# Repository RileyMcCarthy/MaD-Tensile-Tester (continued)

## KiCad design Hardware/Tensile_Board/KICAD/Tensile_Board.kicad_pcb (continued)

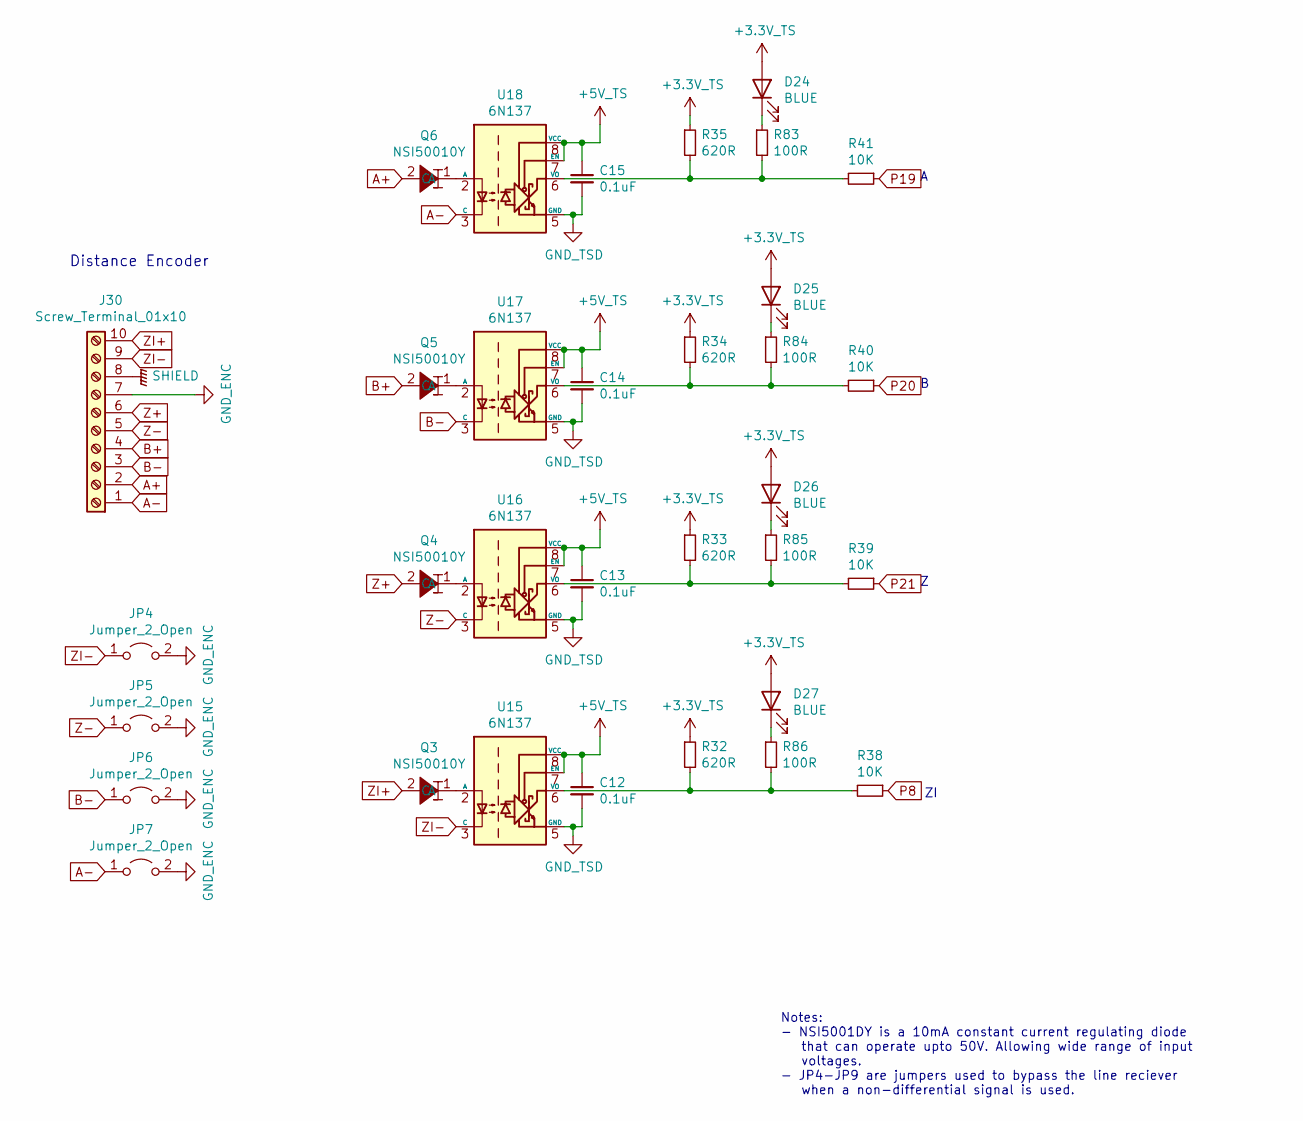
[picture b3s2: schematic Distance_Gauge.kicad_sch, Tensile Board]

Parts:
C12, C13, C14, C15: 0.1uF; C_0603_1608Metric; LCSC C14663
D24, D25, D26, D27: BLUE; LED_0603_1608Metric; LCSC C72041
J30: Screw_Terminal_01x10; TerminalBlock_4Ucon_1x10_P3.50mm_Vertical
JP4, JP5, JP6, JP7: Jumper_2_Open; PinHeader_1x02_P2.54mm_Vertical
Q3, Q4, Q5, Q6: NSI50010Y; D_SOD-123; LCSC C150049
R32, R33, R34, R35: 620R; R_0603_1608Metric; LCSC C23138
R38, R39, R40, R41: 10K; R_0603_1608Metric; LCSC C25804
R83, R84, R85, R86: 100R; R_0603_1608Metric; LCSC C22775
U15, U16, U17, U18: 6N137; SOP-8_6.62x9.15mm_P2.54mm; LCSC C110020

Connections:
GND_ENC: J30.7, JP4.2 (B), JP5.2 (B), JP6.2 (B), JP7.2 (B)
GND_TSD: C12.2, C13.2, C14.2, C15.2, U15.5 (GND), U16.5 (GND), U17.5 (GND), U18.5 (GND); also elsewhere on the board
unnamed: D24.1 (K), R83.1
unnamed: D25.1 (K), R84.1
unnamed: D26.1 (K), R85.1
unnamed: D27.1 (K), R86.1
unnamed: Q3.1 (C), U15.2 (A)
unnamed: Q4.1 (C), U16.2 (A)
unnamed: Q5.1 (C), U17.2 (A)
unnamed: Q6.1 (C), U18.2 (A)
unnamed: R32.2, R38.2, R86.2, U15.6 (VO)
unnamed: R33.2, R39.2, R85.2, U16.6 (VO)
unnamed: R34.2, R40.2, R84.2, U17.6 (VO)
unnamed: R35.2, R41.2, R83.2, U18.6 (VO)
OUTA+: J30.2, Q6.2 (A)
OUTA-: J30.1, JP7.1 (A), U18.3 (C)
OUTB+: J30.4, Q5.2 (A)
OUTB-: J30.3, JP6.1 (A), U17.3 (C)
OUTZ+: J30.6, Q4.2 (A)
OUTZ-: J30.5, JP5.1 (A), U16.3 (C)
OUTZI+: J30.10, Q3.2 (A)
OUTZI-: J30.9, JP4.1 (A), U15.3 (C)
P8: R38.1; also elsewhere on the board
P19: R41.1; also elsewhere on the board
P20: R40.1; also elsewhere on the board
P21: R39.1; also elsewhere on the board
SHIELD: J30.8; also elsewhere on the board

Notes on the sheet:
Notes: - NSI5001DY is a 10mA constant current regulating diode that can operate upto 50V. Allowing wide range of input voltages. - JP4-JP9 are jumpers used to bypass the line reciever when a non-differential signal is used.
Distance Encoder

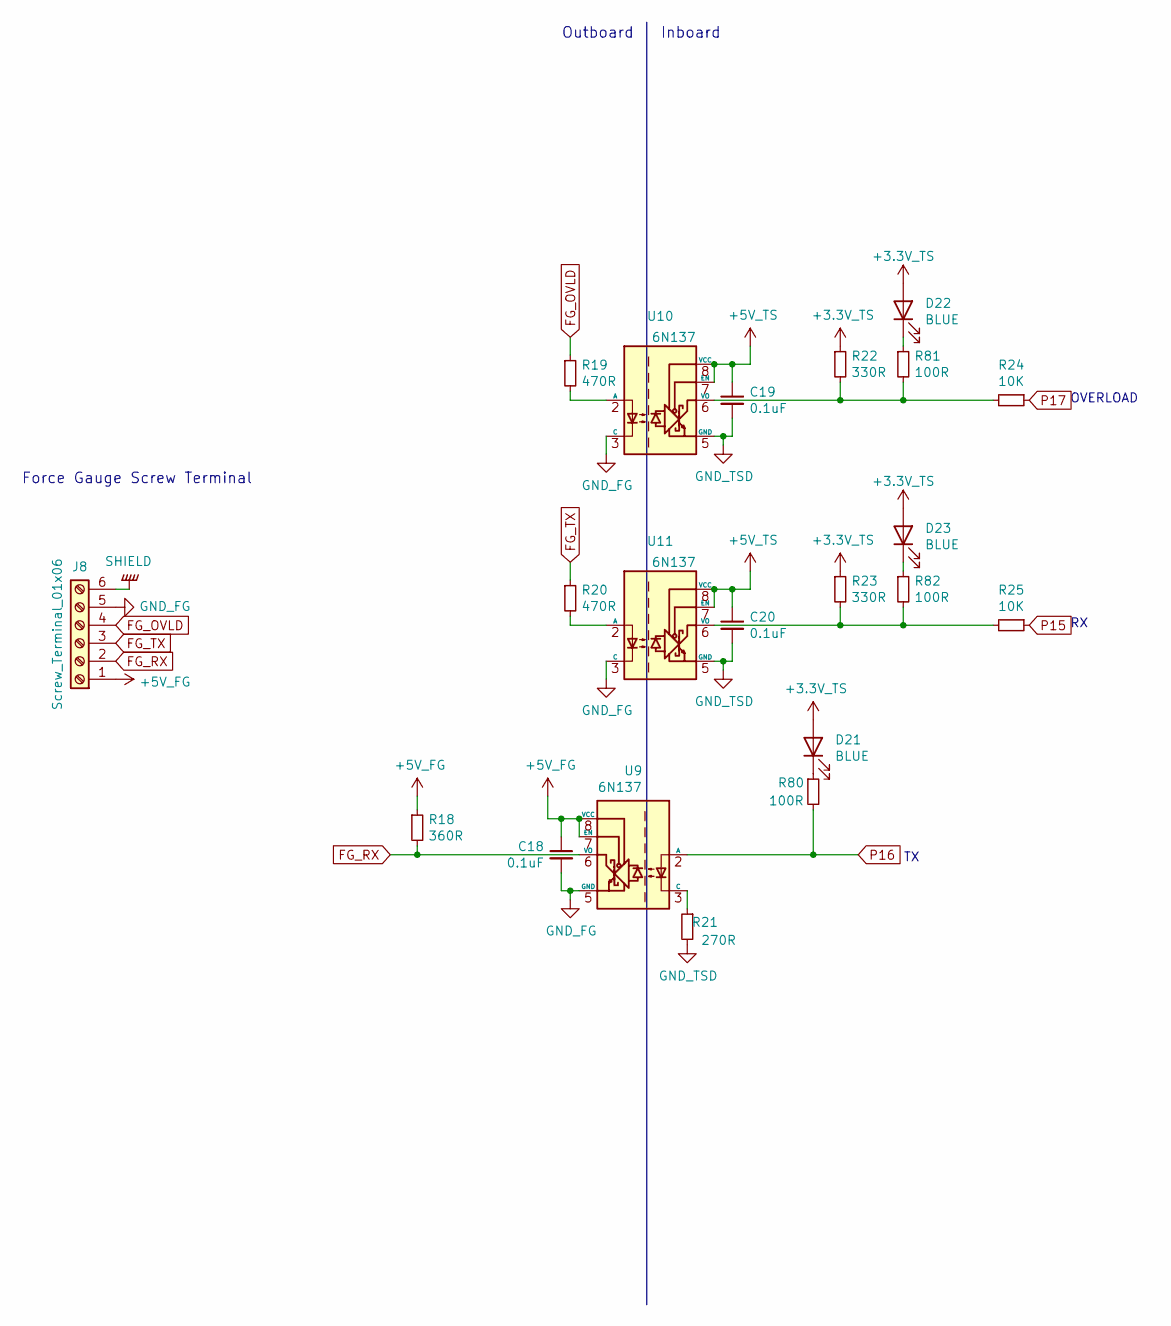
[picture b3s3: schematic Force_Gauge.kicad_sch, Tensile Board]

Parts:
C18, C19, C20: 0.1uF; C_0603_1608Metric; LCSC C14663
D21, D22, D23: BLUE; LED_0603_1608Metric; LCSC C72041
J8: Screw_Terminal_01x06; TerminalBlock_4Ucon_1x06_P3.50mm_Vertical
R18: 360R; R_0603_1608Metric; LCSC C25194
R19, R20: 470R; R_0603_1608Metric; LCSC C23179
R21: 270R; R_0603_1608Metric; LCSC C22966
R22, R23: 330R; R_0603_1608Metric; LCSC C23138
R24, R25: 10K; R_0603_1608Metric; LCSC C25804
R80, R81, R82: 100R; R_0603_1608Metric; LCSC C22775
U9, U10, U11: 6N137; SOP-8_6.62x9.15mm_P2.54mm; LCSC C110020

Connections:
+5V_FG: C18.1, J8.1, R18.1, U9.7 (EN), U9.8 (VCC)
FG_OVLD: J8.4, R19.1
FG_RX: J8.2, R18.2, U9.6 (VO)
FG_TX: J8.3, R20.1
GND_FG: C18.2, J8.5, U9.5 (GND), U10.3 (C), U11.3 (C)
GND_TSD: C19.2, C20.2, R21.2, U10.5 (GND), U11.5 (GND); also elsewhere on the board
unnamed: D21.1 (K), R80.1
unnamed: D22.1 (K), R81.1
unnamed: D23.1 (K), R82.1
unnamed: R19.2, U10.2 (A)
unnamed: R20.2, U11.2 (A)
unnamed: R21.1, U9.3 (C)
unnamed: R22.2, R24.2, R81.2, U10.6 (VO)
unnamed: R23.2, R25.2, R82.2, U11.6 (VO)
P15: R25.1; also elsewhere on the board
P16: R80.2, U9.2 (A); also elsewhere on the board
P17: R24.1; also elsewhere on the board
SHIELD: J8.6; also elsewhere on the board

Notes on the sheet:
OVERLOAD
Outboard
Inboard
Force Gauge Screw Terminal

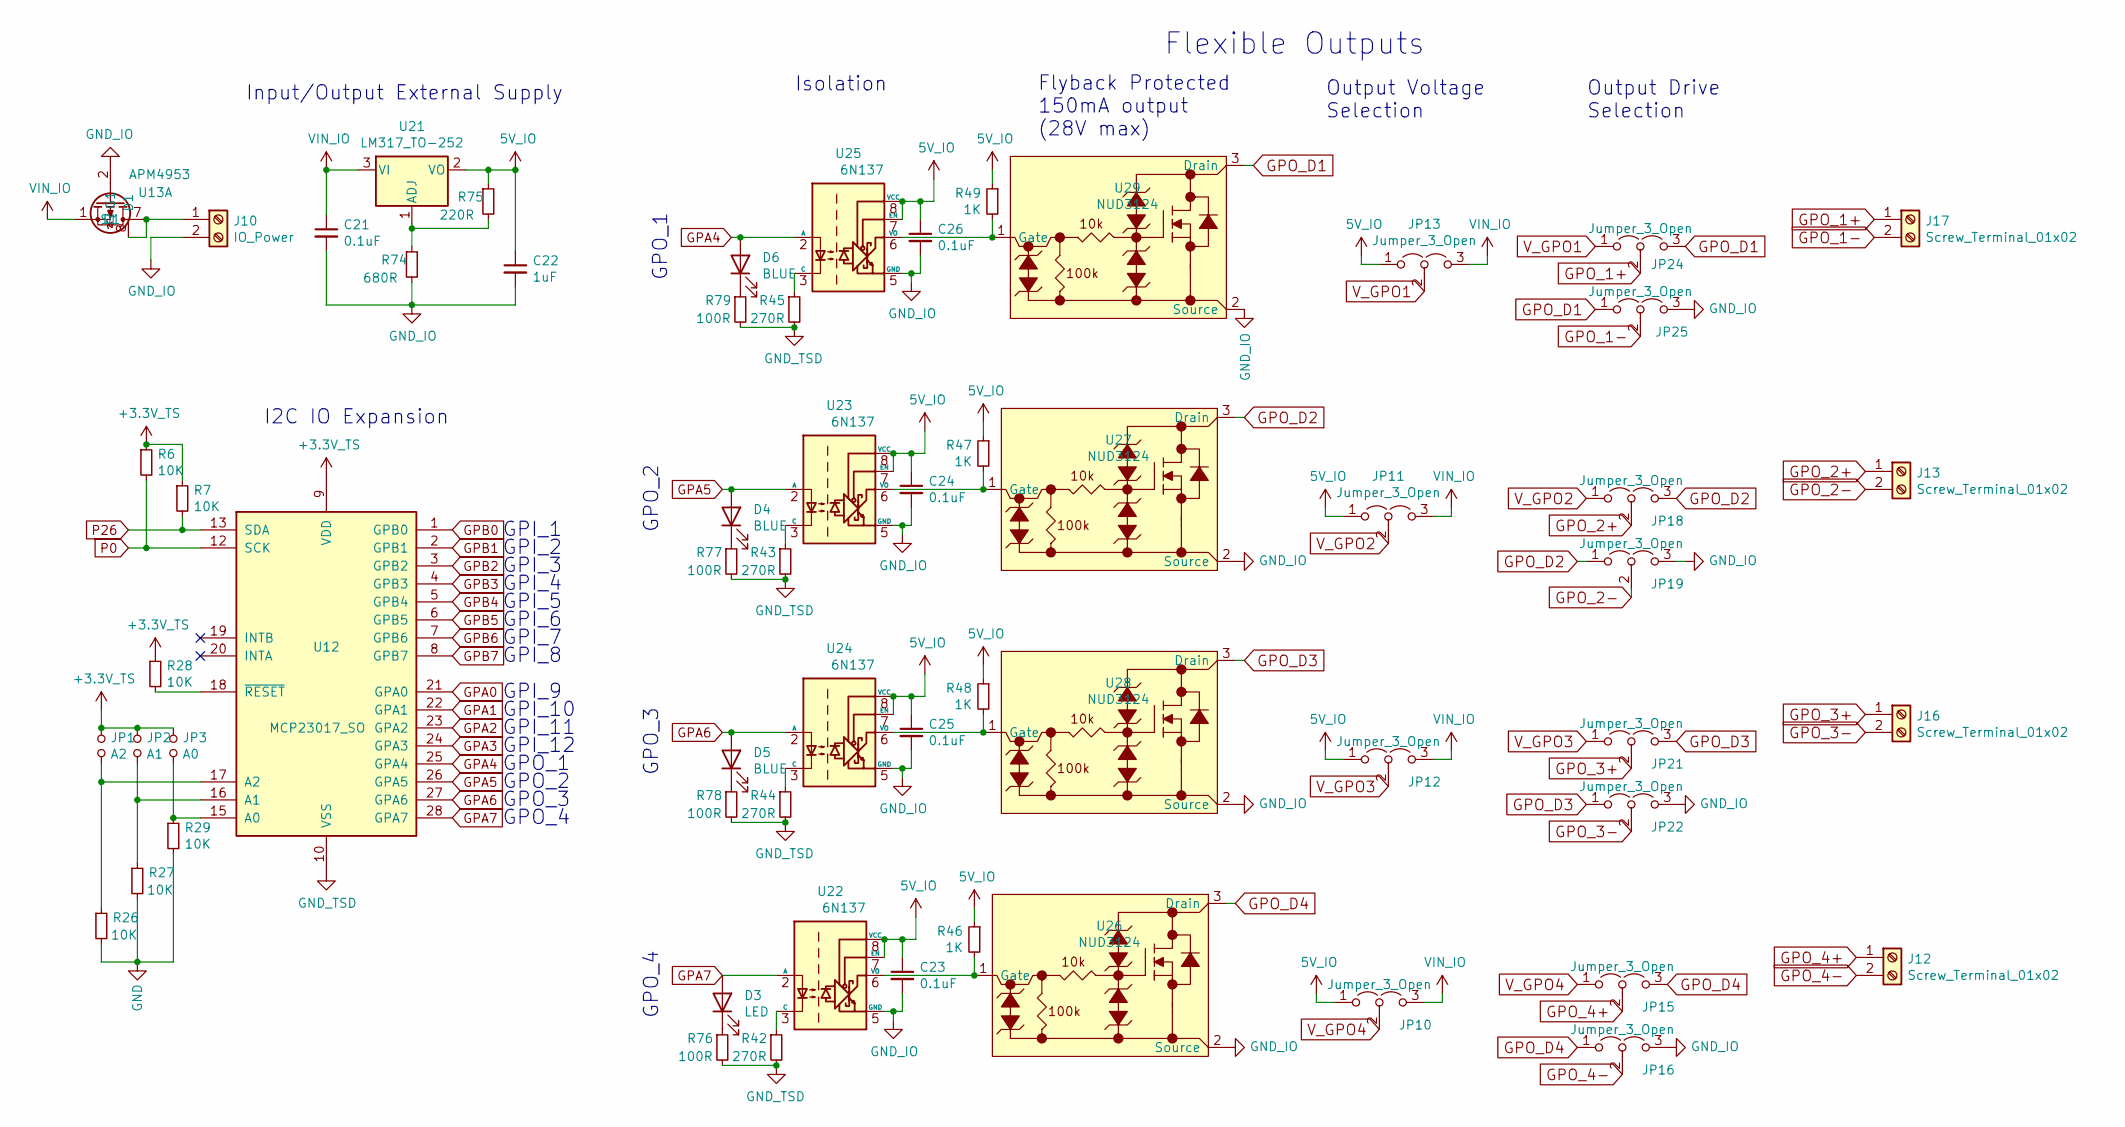
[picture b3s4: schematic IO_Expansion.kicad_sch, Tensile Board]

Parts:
C21: 0.1uF; C_0805_2012Metric; LCSC C49678
C22: 1uF; C_0805_2012Metric; LCSC C28323
C23, C24, C25, C26: 0.1uF; C_0603_1608Metric; LCSC C14663
D3: LED; LED_0603_1608Metric; LCSC C72041
D4, D5, D6: BLUE; LED_0603_1608Metric; LCSC C72041
J10: IO_Power; TerminalBlock_bornier-2_P5.08mm
J12, J13, J16, J17: Screw_Terminal_01x02; TerminalBlock_4Ucon_1x02_P3.50mm_Vertical
JP1: A2; SolderJumper-2_P1.3mm_Open_Pad1.0x1.5mm
JP2: A1; SolderJumper-2_P1.3mm_Open_Pad1.0x1.5mm
JP3: A0; SolderJumper-2_P1.3mm_Open_Pad1.0x1.5mm
JP10, JP11, JP12, JP13, JP15, JP16, JP18, JP19, JP21, JP22, JP24, JP25: Jumper_3_Open; PinHeader_1x03_P2.54mm_Vertical
R6, R7, R26, R27, R28, R29: 10K; R_0603_1608Metric; LCSC C25804
R42, R43, R44, R45: 270R; R_0603_1608Metric; LCSC C22966
R46, R47, R48, R49: 1K; R_0603_1608Metric; LCSC C21190
R74: 680R; R_0603_1608Metric; LCSC C23228
R75: 220R; R_0603_1608Metric; LCSC C22962
R76, R77, R78, R79: 100R; R_0603_1608Metric; LCSC C22775
U12: MCP23017_SO; SOIC-28W_7.5x17.9mm_P1.27mm; LCSC C47023
U13: APM4953; SOP-8_3.9x4.9mm_P1.27mm; LCSC C20897
U21: LM317_TO-252; TO-252-2; LCSC C75510
U22, U23, U24, U25: 6N137; SOP-8_6.62x9.15mm_P2.54mm; LCSC C110020
U26, U27, U28, U29: NUD3124; SOT-23; LCSC C85758

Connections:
5V_IO: C22.1, C23.1, C24.1, C25.1, C26.1, JP10.1 (A), JP11.1 (A), JP12.1 (A), JP13.1 (A), R46.1, R47.1, R48.1, R49.1, R75.1, U21.2 (VO), U22.7 (EN), U22.8 (VCC), U23.7 (EN), U23.8 (VCC), U24.7 (EN), U24.8 (VCC), U25.7 (EN), U25.8 (VCC); also elsewhere on the board
GND: R26.2, R27.2, R29.2
GND_IO: C21.2, C22.2, C23.2, C24.2, C25.2, C26.2, J10.2, JP16.3 (B), JP19.3 (B), JP22.3 (B), JP25.3 (B), R74.2, U13.2 (G1), U22.5 (GND), U23.5 (GND), U24.5 (GND), U25.5 (GND), U26.2 (Source), U27.2 (Source), U28.2 (Source), U29.2 (Source); also elsewhere on the board
GND_TSD: R42.2, R43.2, R44.2, R45.2, R76.2, R77.2, R78.2, R79.2, U12.10 (VSS); also elsewhere on the board
GPA0: U12.21 (GPA0); also elsewhere on the board
GPA1: U12.22 (GPA1); also elsewhere on the board
GPA2: U12.23 (GPA2); also elsewhere on the board
GPA3: U12.24 (GPA3); also elsewhere on the board
GPA4: D6.2 (A), U12.25 (GPA4), U25.2 (A)
GPA5: D4.2 (A), U12.26 (GPA5), U23.2 (A)
GPA6: D5.2 (A), U12.27 (GPA6), U24.2 (A)
GPA7: D3.2 (A), U12.28 (GPA7), U22.2 (A)
GPB0: U12.1 (GPB0); also elsewhere on the board
GPB1: U12.2 (GPB1); also elsewhere on the board
GPB2: U12.3 (GPB2); also elsewhere on the board
GPB3: U12.4 (GPB3); also elsewhere on the board
GPB4: U12.5 (GPB4); also elsewhere on the board
GPB5: U12.6 (GPB5); also elsewhere on the board
GPB6: U12.7 (GPB6); also elsewhere on the board
GPB7: U12.8 (GPB7); also elsewhere on the board
GPO_1+: J17.1, JP24.2 (C)
GPO_1-: J17.2, JP25.2 (C)
GPO_2+: J13.1, JP18.2 (C)
GPO_2-: J13.2, JP19.2 (C)
GPO_3+: J16.1, JP21.2 (C)
GPO_3-: J16.2, JP22.2 (C)
GPO_4+: J12.1, JP15.2 (C)
GPO_4-: J12.2, JP16.2 (C)
GPO_D1: JP24.3 (B), JP25.1 (A), U29.3 (Drain)
GPO_D2: JP18.3 (B), JP19.1 (A), U27.3 (Drain)
GPO_D3: JP21.3 (B), JP22.1 (A), U28.3 (Drain)
GPO_D4: JP15.3 (B), JP16.1 (A), U26.3 (Drain)
unnamed: D3.1 (K), R76.1
unnamed: D4.1 (K), R77.1
unnamed: D5.1 (K), R78.1
unnamed: D6.1 (K), R79.1
unnamed: J10.1, U13.7 (D1), U13.8 (D1)
unnamed: JP1.2, R26.1, U12.17 (A2)
unnamed: JP2.2, R27.1, U12.16 (A1)
unnamed: JP3.2, R29.1, U12.15 (A0)
unnamed: R28.2, U12.18 (~RESET)
unnamed: R42.1, U22.3 (C)
unnamed: R43.1, U23.3 (C)
unnamed: R44.1, U24.3 (C)
unnamed: R45.1, U25.3 (C)
unnamed: R46.2, U22.6 (VO), U26.1 (Gate)
unnamed: R47.2, U23.6 (VO), U27.1 (Gate)
unnamed: R48.2, U24.6 (VO), U28.1 (Gate)
unnamed: R49.2, U25.6 (VO), U29.1 (Gate)
unnamed: R74.1, R75.2, U21.1 (ADJ)
VIN_IO: C21.1, JP10.3 (B), JP11.3 (B), JP12.3 (B), JP13.3 (B), U13.1 (S1), U21.3 (VI)
V_GPO1: JP13.2 (C), JP24.1 (A)
V_GPO2: JP11.2 (C), JP18.1 (A)
V_GPO3: JP12.2 (C), JP21.1 (A)
V_GPO4: JP10.2 (C), JP15.1 (A)

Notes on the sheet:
GPI_6
GPO_3
GPI_4
Output Voltage Selection
GPI_11
Flexible Outputs
GPI_7
GPI_10
Input/Output External Supply
GPI_3
GPI_9
GPO_2
GPO_1
I2C IO Expansion
GPI_1
GPO_4
GPI_12
GPI_8
GPI_5
GPI_2
Isolation
Output Drive Selection
Flyback Protected 150mA output (28V max)

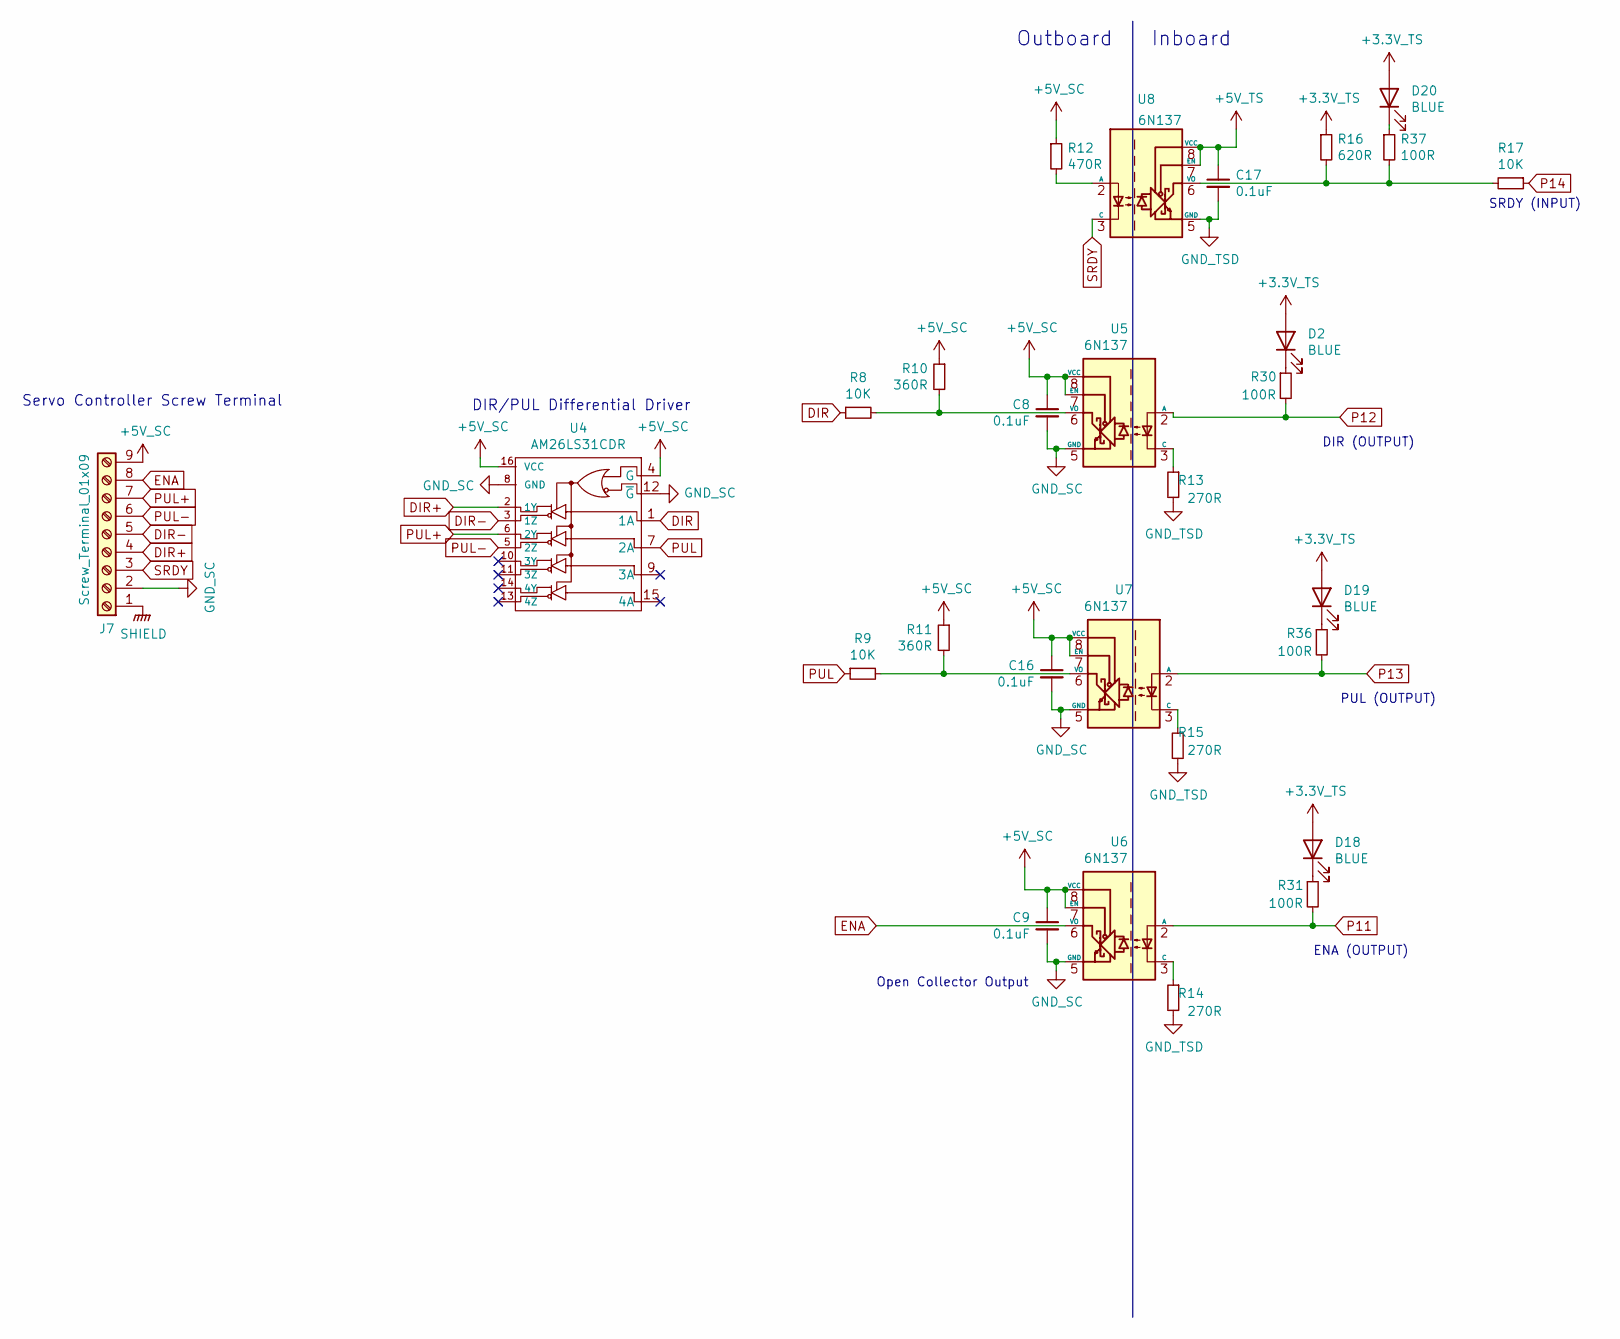
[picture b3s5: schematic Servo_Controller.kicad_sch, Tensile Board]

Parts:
C8, C9, C16, C17: 0.1uF; C_0603_1608Metric; LCSC C14663
D2, D18, D19, D20: BLUE; LED_0603_1608Metric; LCSC C72041
J7: Screw_Terminal_01x09; TerminalBlock_4Ucon_1x09_P3.50mm_Vertical
R8, R9, R17: 10K; R_0603_1608Metric; LCSC C25804
R10, R11: 360R; R_0603_1608Metric; LCSC C25194
R12: 470R; R_0603_1608Metric; LCSC C23179
R13, R14, R15: 270R; R_0603_1608Metric; LCSC C22966
R16: 620R; R_0603_1608Metric; LCSC C23138
R30, R31, R36, R37: 100R; R_0603_1608Metric; LCSC C22775
U4: AM26LS31CDR; SOIC-16_3.9x9.9mm_P1.27mm; LCSC C6179
U5, U6, U7, U8: 6N137; SOP-8_6.62x9.15mm_P2.54mm; LCSC C110020

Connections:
+5V_SC: C8.1, C9.1, C16.1, J7.9, R10.1, R11.1, R12.1, U4.4 (G), U4.16 (VCC), U5.7 (EN), U5.8 (VCC), U6.7 (EN), U6.8 (VCC), U7.7 (EN), U7.8 (VCC)
DIR: R8.1, U4.1 (1A)
DIR+: J7.4, U4.2 (1Y)
DIR-: J7.5, U4.3 (1Z)
ENA: J7.8, U6.6 (VO)
GND_SC: C8.2, C9.2, C16.2, J7.2, U4.8 (GND), U4.12 (~G), U5.5 (GND), U6.5 (GND), U7.5 (GND)
GND_TSD: C17.2, R13.2, R14.2, R15.2, U8.5 (GND); also elsewhere on the board
unnamed: D2.1 (K), R30.1
unnamed: D18.1 (K), R31.1
unnamed: D19.1 (K), R36.1
unnamed: D20.1 (K), R37.1
unnamed: R8.2, R10.2, U5.6 (VO)
unnamed: R9.2, R11.2, U7.6 (VO)
unnamed: R12.2, U8.2 (A)
unnamed: R13.1, U5.3 (C)
unnamed: R14.1, U6.3 (C)
unnamed: R15.1, U7.3 (C)
unnamed: R16.2, R17.2, R37.2, U8.6 (VO)
P11: R31.2, U6.2 (A); also elsewhere on the board
P12: R30.2, U5.2 (A); also elsewhere on the board
P13: R36.2, U7.2 (A); also elsewhere on the board
P14: R17.1; also elsewhere on the board
PUL: R9.1, U4.7 (2A)
PUL+: J7.7, U4.6 (2Y)
PUL-: J7.6, U4.5 (2Z)
SHIELD: J7.1; also elsewhere on the board
SRDY: J7.3, U8.3 (C)

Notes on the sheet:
Inboard
Servo Controller Screw Terminal
PUL (OUTPUT)
DIR (OUTPUT)
SRDY (INPUT)
DIR/PUL Differential Driver
Open Collector Output
ENA (OUTPUT)
Outboard

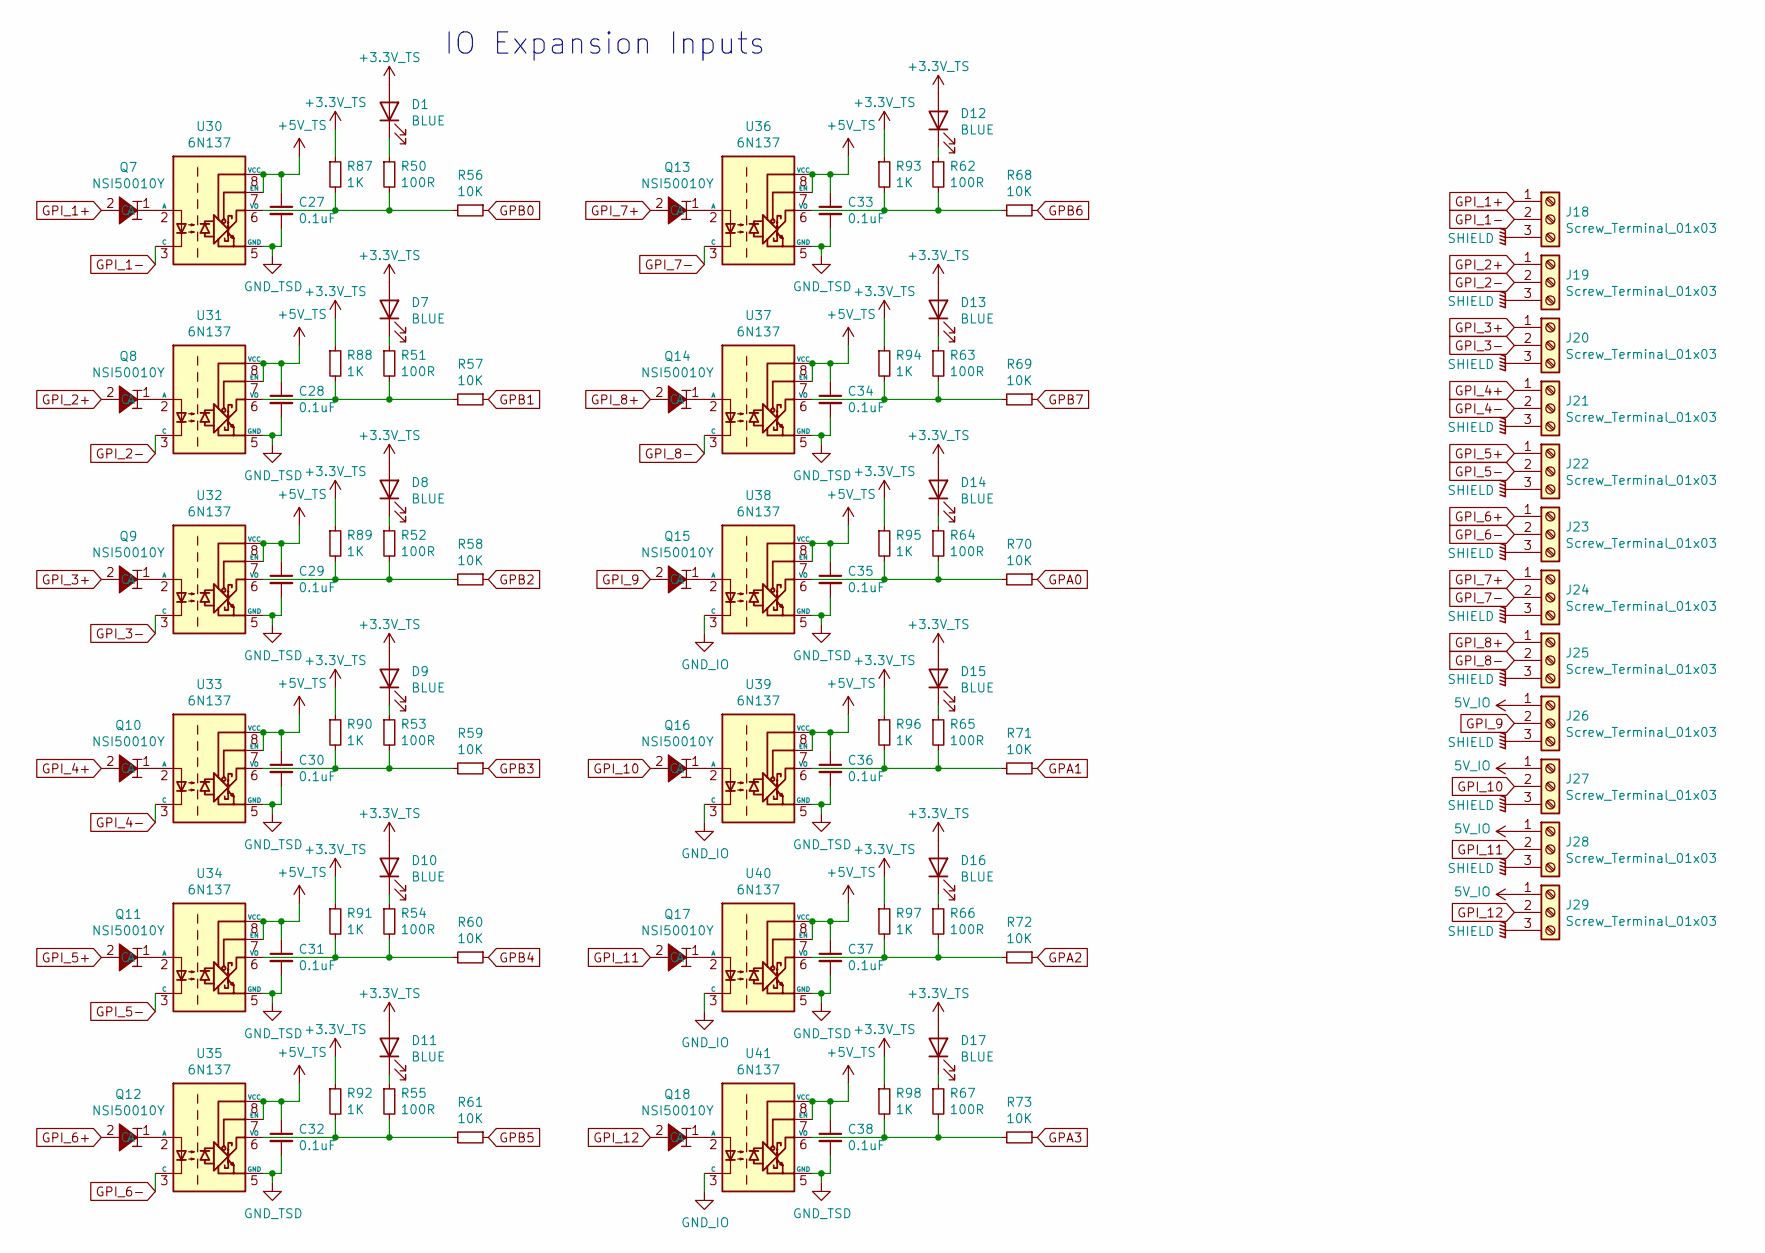
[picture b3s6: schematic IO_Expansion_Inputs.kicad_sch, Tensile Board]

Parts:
C27, C28, C29, C30, C31, C32, C33, C34, C35, C36, C37, C38: 0.1uF; C_0603_1608Metric; LCSC C14663
D1, D7, D8, D9, D10, D11, D12, D13, D14, D15, D16, D17: BLUE; LED_0603_1608Metric; LCSC C72041
J18, J19, J20, J21, J22, J23, J24, J25, J26, J27, J28, J29: Screw_Terminal_01x03; TerminalBlock_4Ucon_1x03_P3.50mm_Vertical
Q7, Q8, Q9, Q10, Q11, Q12, Q13, Q14, Q15, Q16, Q17, Q18: NSI50010Y; D_SOD-123; LCSC C150049
R50, R51, R52, R53, R54, R55, R62, R63, R64, R65, R66, R67: 100R; R_0603_1608Metric; LCSC C22775
R56, R57, R58, R59, R60, R61, R68, R69, R70, R71, R72, R73: 10K; R_0603_1608Metric; LCSC C25804
R87, R88, R89, R90, R91, R92, R93, R94, R95, R96, R97, R98: 1K; R_0603_1608Metric; LCSC C21190
U30, U31, U32, U33, U34, U35, U36, U37, U38, U39, U40, U41: 6N137; SOP-8_6.62x9.15mm_P2.54mm; LCSC C110020

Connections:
5V_IO: J26.1, J27.1, J28.1, J29.1; also elsewhere on the board
GND_IO: U38.3 (C), U39.3 (C), U40.3 (C), U41.3 (C); also elsewhere on the board
GND_TSD: C27.2, C28.2, C29.2, C30.2, C31.2, C32.2, C33.2, C34.2, C35.2, C36.2, C37.2, C38.2, U30.5 (GND), U31.5 (GND), U32.5 (GND), U33.5 (GND), U34.5 (GND), U35.5 (GND), U36.5 (GND), U37.5 (GND), U38.5 (GND), U39.5 (GND), U40.5 (GND), U41.5 (GND); also elsewhere on the board
GPA0: R70.1; also elsewhere on the board
GPA1: R71.1; also elsewhere on the board
GPA2: R72.1; also elsewhere on the board
GPA3: R73.1; also elsewhere on the board
GPB0: R56.1; also elsewhere on the board
GPB1: R57.1; also elsewhere on the board
GPB2: R58.1; also elsewhere on the board
GPB3: R59.1; also elsewhere on the board
GPB4: R60.1; also elsewhere on the board
GPB5: R61.1; also elsewhere on the board
GPB6: R68.1; also elsewhere on the board
GPB7: R69.1; also elsewhere on the board
GPI_1+: J18.1, Q7.2 (A)
GPI_1-: J18.2, U30.3 (C)
GPI_2+: J19.1, Q8.2 (A)
GPI_2-: J19.2, U31.3 (C)
GPI_3+: J20.1, Q9.2 (A)
GPI_3-: J20.2, U32.3 (C)
GPI_4+: J21.1, Q10.2 (A)
GPI_4-: J21.2, U33.3 (C)
GPI_5+: J22.1, Q11.2 (A)
GPI_5-: J22.2, U34.3 (C)
GPI_6+: J23.1, Q12.2 (A)
GPI_6-: J23.2, U35.3 (C)
GPI_7+: J24.1, Q13.2 (A)
GPI_7-: J24.2, U36.3 (C)
GPI_8+: J25.1, Q14.2 (A)
GPI_8-: J25.2, U37.3 (C)
GPI_9: J26.2, Q15.2 (A)
GPI_10: J27.2, Q16.2 (A)
GPI_11: J28.2, Q17.2 (A)
GPI_12: J29.2, Q18.2 (A)
unnamed: D1.1 (K), R50.1
unnamed: D7.1 (K), R51.1
unnamed: D8.1 (K), R52.1
unnamed: D9.1 (K), R53.1
unnamed: D10.1 (K), R54.1
unnamed: D11.1 (K), R55.1
unnamed: D12.1 (K), R62.1
unnamed: D13.1 (K), R63.1
unnamed: D14.1 (K), R64.1
unnamed: D15.1 (K), R65.1
unnamed: D16.1 (K), R66.1
unnamed: D17.1 (K), R67.1
unnamed: Q7.1 (C), U30.2 (A)
unnamed: Q8.1 (C), U31.2 (A)
unnamed: Q9.1 (C), U32.2 (A)
unnamed: Q10.1 (C), U33.2 (A)
unnamed: Q11.1 (C), U34.2 (A)
unnamed: Q12.1 (C), U35.2 (A)
unnamed: Q13.1 (C), U36.2 (A)
unnamed: Q14.1 (C), U37.2 (A)
unnamed: Q15.1 (C), U38.2 (A)
unnamed: Q16.1 (C), U39.2 (A)
unnamed: Q17.1 (C), U40.2 (A)
unnamed: Q18.1 (C), U41.2 (A)
unnamed: R50.2, R56.2, R87.2, U30.6 (VO)
unnamed: R51.2, R57.2, R88.2, U31.6 (VO)
unnamed: R52.2, R58.2, R89.2, U32.6 (VO)
unnamed: R53.2, R59.2, R90.2, U33.6 (VO)
unnamed: R54.2, R60.2, R91.2, U34.6 (VO)
unnamed: R55.2, R61.2, R92.2, U35.6 (VO)
unnamed: R62.2, R68.2, R93.2, U36.6 (VO)
unnamed: R63.2, R69.2, R94.2, U37.6 (VO)
unnamed: R64.2, R70.2, R95.2, U38.6 (VO)
unnamed: R65.2, R71.2, R96.2, U39.6 (VO)
unnamed: R66.2, R72.2, R97.2, U40.6 (VO)
unnamed: R67.2, R73.2, R98.2, U41.6 (VO)
SHIELD: J18.3, J19.3, J20.3, J21.3, J22.3, J23.3, J24.3, J25.3, J26.3, J27.3, J28.3, J29.3; also elsewhere on the board

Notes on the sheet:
IO Expansion Inputs

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
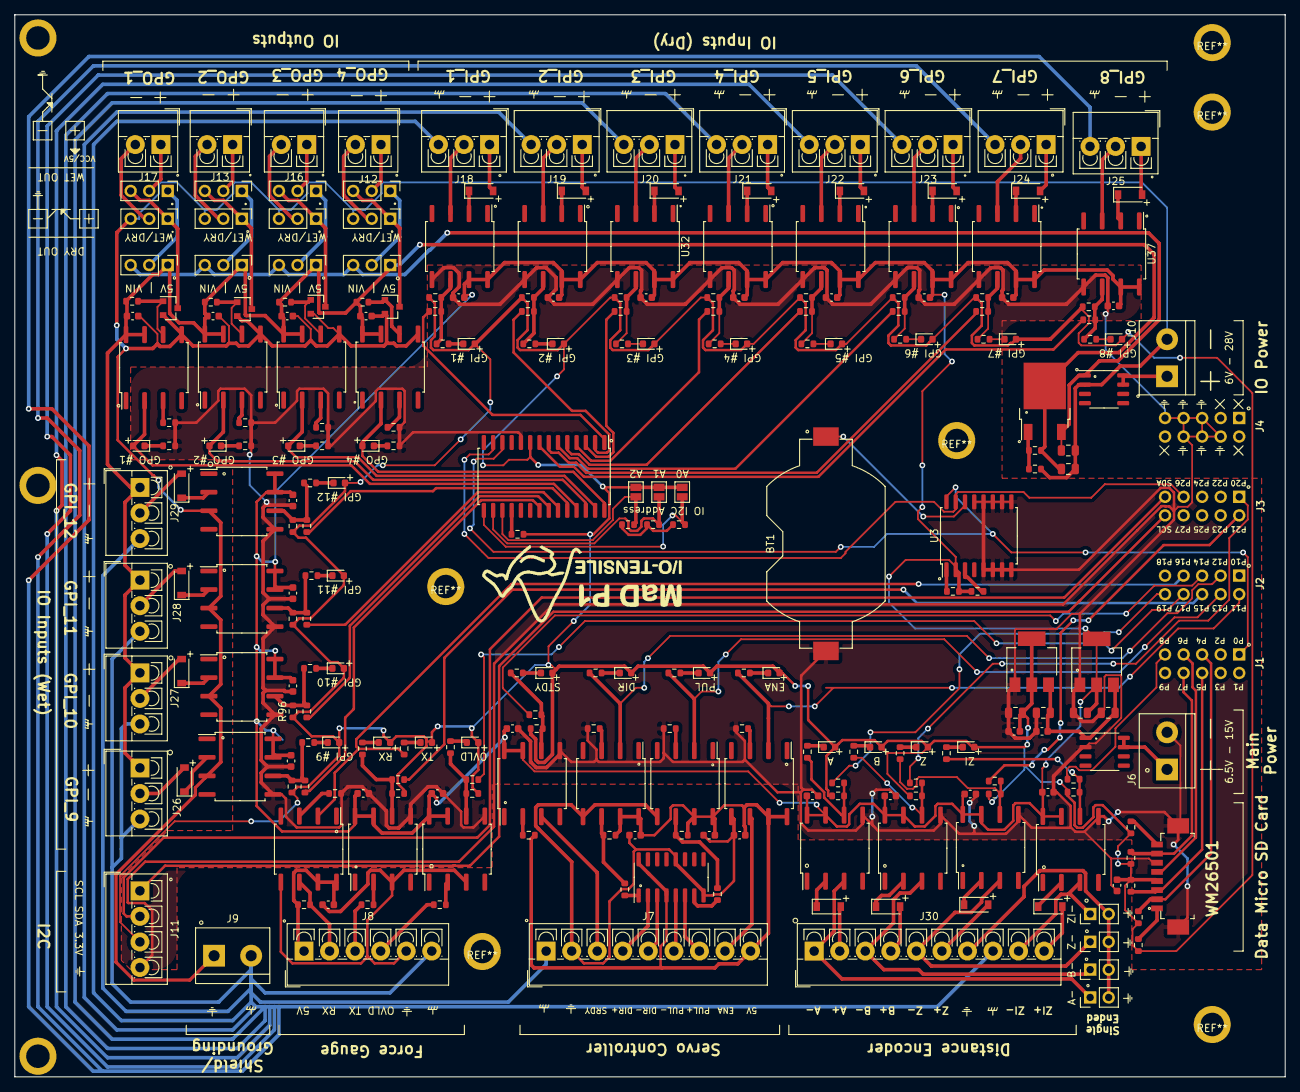
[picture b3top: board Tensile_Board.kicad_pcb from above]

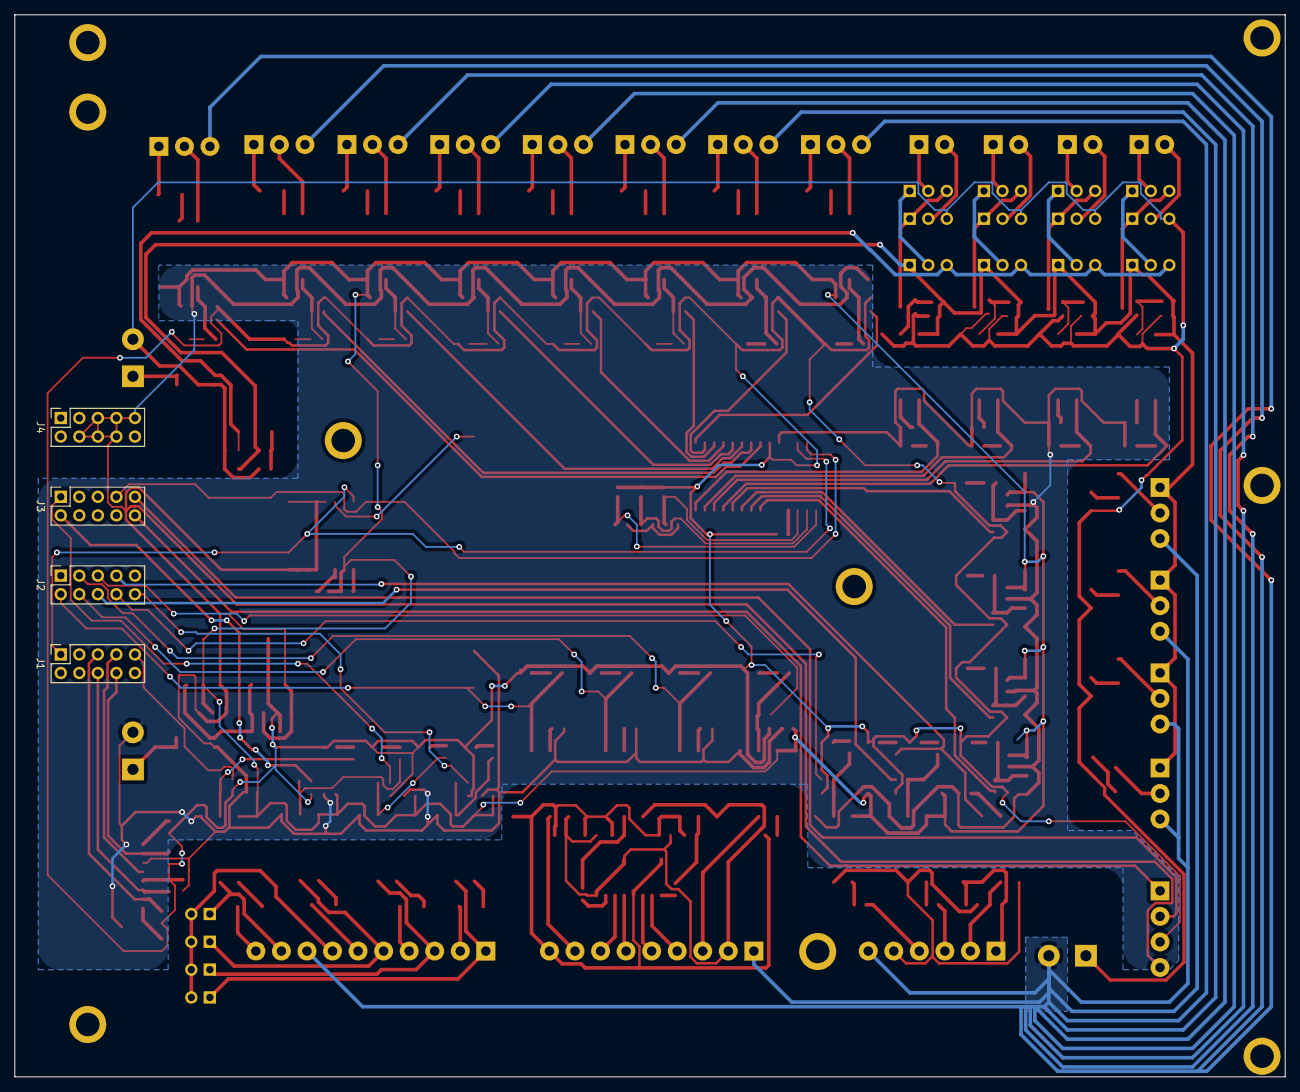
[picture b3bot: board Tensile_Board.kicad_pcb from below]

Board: 2 copper layers, 174.0 x 145.5 mm, 268 parts (4 on the bottom side), 195 nets.

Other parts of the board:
C2, C3: 10uF; C_0805_2012Metric
C4, C6: 4.7uF; C_0805_2012Metric
C5, C7: 1uF; C_0603_1608Metric
DISP_HOLE_1, DISP_HOLE_2, DISP_HOLE_3: Hole_5.08
LOGO: LOGO_1
U1: AMS1117-5.0; SOT-223-3_TabPin2
U2: AMS1117-3.3; SOT-223-3_TabPin2

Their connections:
GND_TSD: C2.2, C3.2, C4.2, C5.2, C6.2, C7.2, U1.1, U2.1; also elsewhere on the board
V_IN: C2.1, C4.1, C5.1, U1.3, U2.3; also elsewhere on the board
